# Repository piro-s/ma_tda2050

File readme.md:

# Music amplifier on TDA2050:  
A simple two-channel amplifier on a chip TDA2050.  

### Schemes:  
###### ma_tda2050_v0.1:  
[pdf](docs/ma_tda2050_v0.1.pdf)  

### Images:  
###### ma_tda2050_v0.1:  
top:  
  
bottom:  

###### gerber:  
Archive for production:  
[ma_tda2050_v0.1](https://github.com/piro-s/ma_tda2050/raw/main/gerber/ma_tda2050_v0.1.zip)

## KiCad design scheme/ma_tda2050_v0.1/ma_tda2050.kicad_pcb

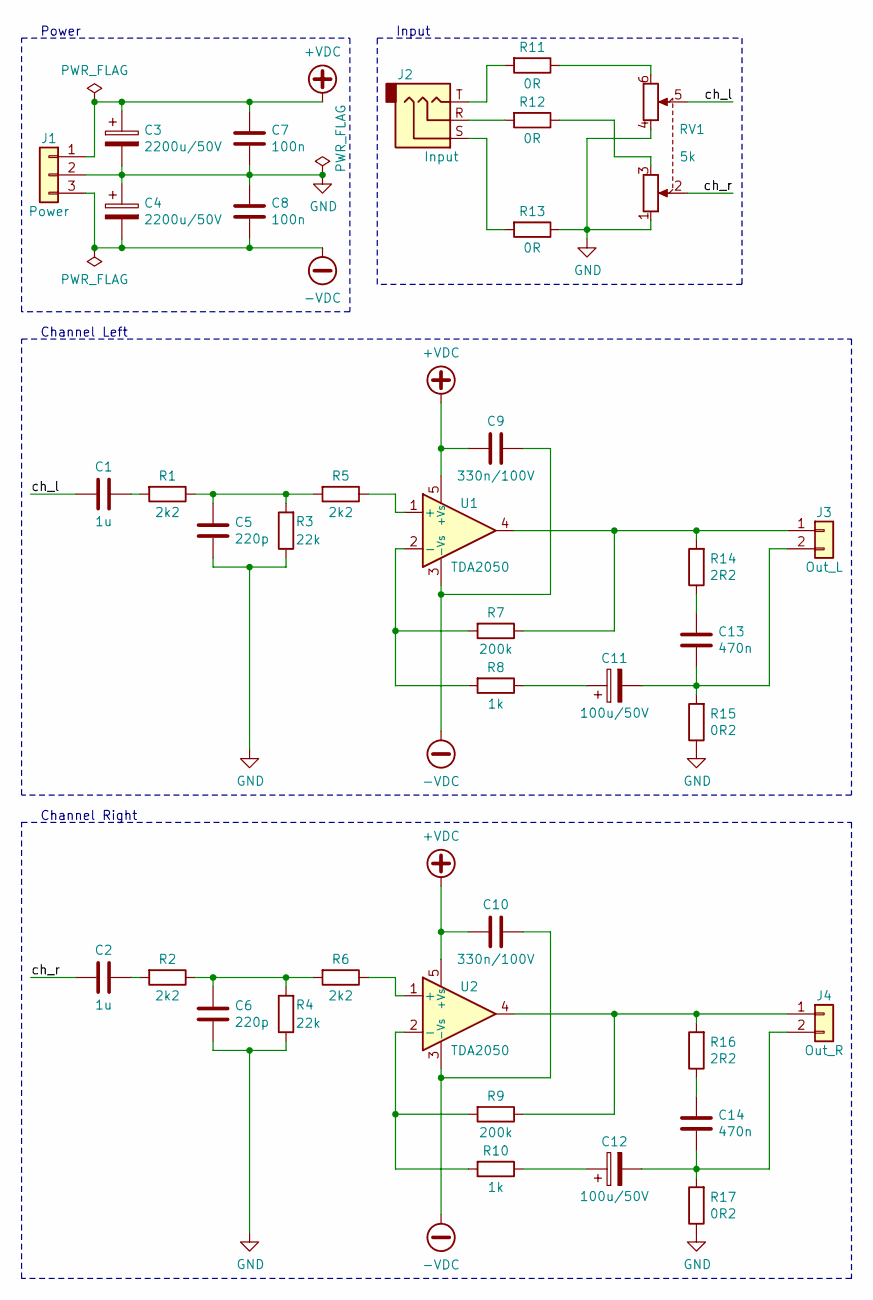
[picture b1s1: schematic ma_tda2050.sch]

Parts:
C1, C2: 1u; C_0603_1608Metric_Pad1.08x0.95mm_HandSolder
C3, C4: 2200u/50V; CP_Radial_D16.0mm_P7.50mm
C5, C6: 220p; C_0603_1608Metric_Pad1.08x0.95mm_HandSolder
C7, C8: 100n; C_0603_1608Metric_Pad1.08x0.95mm_HandSolder
C9, C10: 330n/100V; C_1206_3216Metric_Pad1.33x1.80mm_HandSolder
C11, C12: 100u/50V; CP_Radial_D6.3mm_P2.50mm
C13, C14: 470n; C_0603_1608Metric_Pad1.08x0.95mm_HandSolder
J1: Power; SolderWire-0.5sqmm_1x03_P4.6mm_D0.9mm_OD2.1mm
J2: Input; Jack_3.5mm_PJ322
J3: Out_L; MMCX_Molex_73415-1471_Vertical
J4: Out_R; MMCX_Molex_73415-1471_Vertical
R1, R2, R5, R6: 2k2; R_0603_1608Metric_Pad0.98x0.95mm_HandSolder
R3, R4: 22k; R_0603_1608Metric_Pad0.98x0.95mm_HandSolder
R7, R9: 200k; R_0603_1608Metric_Pad0.98x0.95mm_HandSolder
R8, R10: 1k; R_0603_1608Metric_Pad0.98x0.95mm_HandSolder
R11, R12, R13: 0R; R_0603_1608Metric_Pad0.98x0.95mm_HandSolder
R14, R16: 2R2; R_Axial_DIN0617_L17.0mm_D6.0mm_P20.32mm_Horizontal
R15, R17: 0R2; R_Axial_DIN0617_L17.0mm_D6.0mm_P20.32mm_Horizontal
RV1: 5k; Potentiometer_Alps_RK163_Dual_Horizontal
U1, U2: TDA2050; TO-220-5_P3.4x3.7mm_StaggerOdd_Lead3.8mm_Vertical

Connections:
+VDC: C3.1, C7.1, C9.2, C10.2, J1.1, U1.5 (+Vs), U2.5 (+Vs)
-VDC: C4.2, C8.2, C9.1, C10.1, J1.3, U1.3 (-Vs), U2.3 (-Vs)
/ch_l: C1.2, RV1.5
/ch_r: C2.2, RV1.2
GND: C3.2, C4.1, C5.2, C6.2, C7.2, C8.1, J1.2, R3.1, R4.1, R13.1, R15.1, R17.1, RV1.1, RV1.4
unnamed: C1.1, R1.2
unnamed: C2.1, R2.2
unnamed: C5.1, R1.1, R3.2, R5.2
unnamed: C6.1, R2.1, R4.2, R6.2
unnamed: C11.1, R8.1
unnamed: C11.2, C13.2, J3.2, R15.2
unnamed: C12.1, R10.1
unnamed: C12.2, C14.2, J4.2, R17.2
unnamed: C13.1, R14.1
unnamed: C14.1, R16.1
unnamed: J2.R, R12.2
unnamed: J2.S, R13.2
unnamed: J2.T, R11.2
unnamed: J3.1, R7.1, R14.2, U1.4
unnamed: J4.1, R9.1, R16.2, U2.4
unnamed: R5.1, U1.1 (+)
unnamed: R6.1, U2.1 (+)
unnamed: R7.2, R8.2, U1.2 (-)
unnamed: R9.2, R10.2, U2.2 (-)
unnamed: R11.1, RV1.6
unnamed: R12.1, RV1.3

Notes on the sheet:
Power
Channel Left
Input
Channel Right

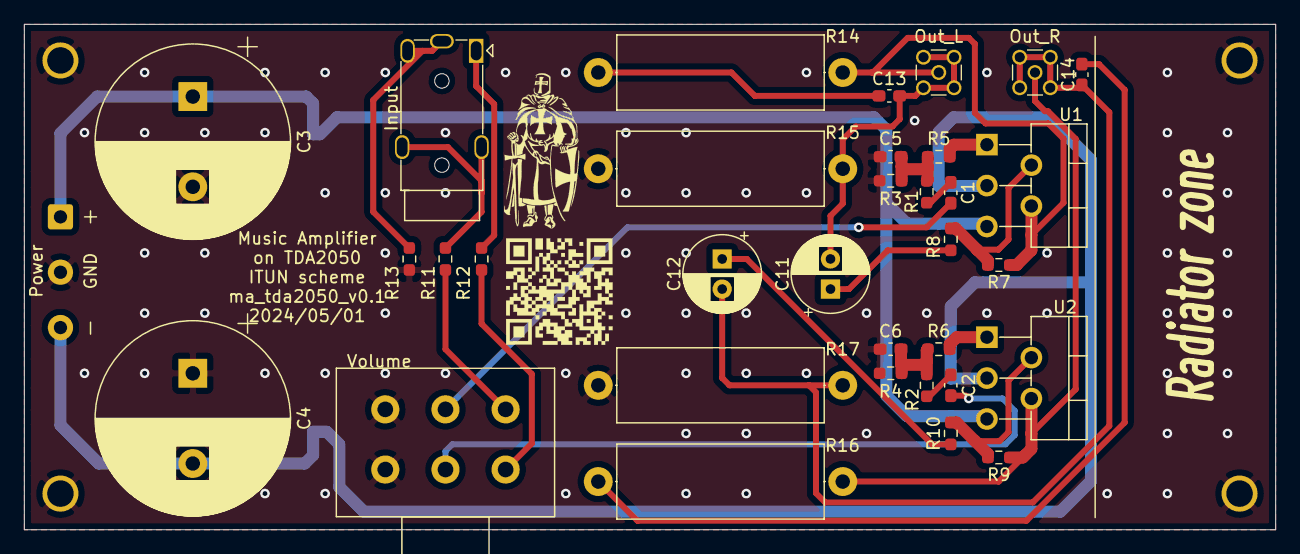
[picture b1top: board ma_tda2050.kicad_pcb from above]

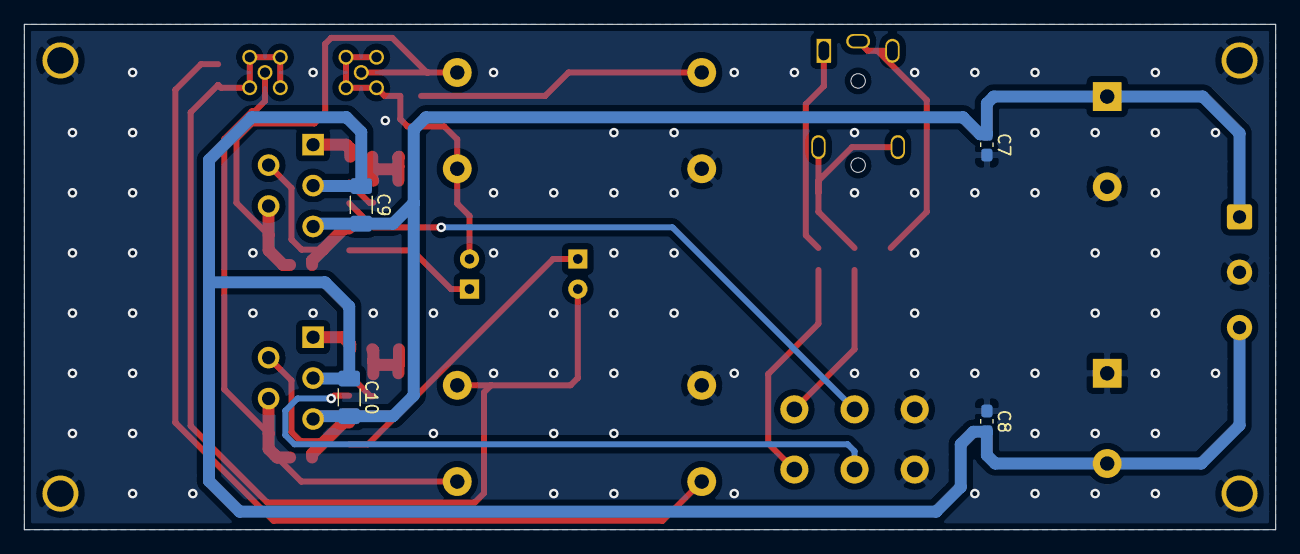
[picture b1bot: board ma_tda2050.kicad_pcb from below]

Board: 2 copper layers, 104.0 x 42.0 mm, 38 parts (4 on the bottom side), 26 nets.

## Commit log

2024-05-01 Initial
2024-05-02 small: QR code
    Change QR code from github to site.
